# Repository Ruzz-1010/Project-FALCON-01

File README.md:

# Project FALCON-01

<!-- FALCON-DOST-REVISION-NOTE:START -->
> **Current revision note (2026-10-10):** Use the DOST major revision baseline in [`docs/REVISION_2026-10-10.md`](docs/REVISION_2026-10-10.md) unless this file is explicitly archived. The active proposal core is a compact ESP32-based buoy with **water pressure sensing, wind speed/direction sensing, GPS for exact position and security, battery + solar power, and Wi-Fi/LTE internet communication**. LoRa, large Bay Station hardware, tall tower layouts, and continuous every-second uploads are legacy or optional fallback assumptions.
<!-- FALCON-DOST-REVISION-NOTE:END -->

## Active design revision 2026-10-10

The current direction is a smaller compact can-buoy with ESP32 local sampling, water pressure sensing, wind speed/direction sensing, GPS position/security, battery + solar power, event-driven summaries and alerts, direct cloud connectivity through Wi-Fi for laboratory work or 4G/LTE for a remote trial, and a reduced battery selected from measured load. LoRa-primary and large Bay Station assumptions are historical unless explicitly marked otherwise.

cd "/home/ruzz/Documents/PlatformIO/Projects/Project FALCON-01/edge"
python3 -m falcon_edge.service

**Fullbright College's AI-powered Live Coastal Observation Network**

Project FALCON is a Phase 1 coastal monitoring buoy proposal focused on five core subsystems:

1. pressure-derived wave/water behavior monitoring;
2. wind speed and wind direction monitoring;
3. GPS-based exact position and security/drift monitoring;
4. battery and solar power monitoring; and
5. Wi-Fi/LTE internet communication for cloud/dashboard reporting.

Short-term wave-height prediction research remains a software-side analysis option and is not run as heavy processing on the buoy.

The AI scope is limited to short-term wave-height prediction and sea-condition classification as **Calm**, **Moderate**, or **Rough**.

## Source of Truth

[PROJECT_CONTEXT.md v9.0](docs/PROJECT_CONTEXT.md) is the official engineering source of truth.

Working source code remains authoritative for what is currently implemented. Documentation describes both the verified prototype and the approved Phase 1 target; it does not turn planned hardware into implemented hardware.

## Current Status

Status: **Phase 1 Prototype**

Implemented in the repository:

- PlatformIO ESP32 Arduino firmware;
- `FALCON-01` Wi-Fi access point and captive portal;
- LittleFS fallback dashboard and basic ESP32 controls;
- laptop-hosted Python edge/cloud service prototype;
- simulated telemetry and deterministic alert scenarios;
- local SQLite telemetry history;
- presentation forecast and backtest pipeline;
- responsive local dashboard with light/dark mode;
- current-versus-predicted forecast presentation;
- browser notifications and alert history;
- and interactive Fusion-derived 3D buoy visualization.

Current mechanical direction: a compact reference-style can buoy with a round float body, tapered top electronics housing, side solar panels, lower ballast, protected pressure stilling tube, LTE/Wi-Fi antenna, red beacon, and single-anchor mooring. Older spar, large tower, and four-outrigger concepts are retained only as historical studies.

### Safe frontend migration

The production dashboard in `data/` remains the verified fallback. The page-by-page React + TypeScript migration in `dashboard-next/` now includes the responsive shell plus Overview, Wave AI, Motion, GPS, Power, System Health, Alerts, Logs, and Settings. Wave AI includes current-versus-predicted results, forecast horizons, model evidence, and presentation scenarios. Motion preserves the Fusion GLB digital twin with telemetry-driven sea motion, camera controls, navigation lights, and component alert highlighting. GPS provides a live Puerto Princesa coastal map, deployment reference, geofence, and drift telemetry. Power presents battery, solar, thermal, fan, and recent-history telemetry. System Health presents local service connectivity, sensor availability, edge resource use, and diagnostics. Alerts provides live notification badges and toasts, active warnings, persisted history, severity filters, and non-destructive acknowledgement. Logs provides searchable telemetry, AI prediction, alert, and system-event archives with filtered CSV/JSON export. Settings provides local presentation preferences, notification permission, scenarios, and auditable maintenance controls.

Run the migration preview with the edge service on port `8765`:

```powershell
cd dashboard-next
npm install
npm run dev
```

Then open `http://127.0.0.1:5173`.

Important limitations:

- physical Phase 1 sensors are not yet fully integrated;
- the laptop currently represents a development cloud/edge host during demonstrations;
- simulator results are not field-validation results;
- the current presentation forecast is not the final trained AI model;
- and the 3D dashboard assets exceed the configured ESP32 LittleFS capacity.

## Approved Phase 1 Architecture

```text
Marine Sensors -> ESP32 -> Wi-Fi/LTE -> Cloud API/database/dashboard
                         |
                         +-> event detection + buffering
                         +-> slow heartbeat summaries
                         +-> immediate alerts on pressure/motion/GPS/power thresholds
                         +-> dashboard -> laptop / tablet / phone
```

Direct cloud connectivity is the revised Phase 1 direction. Wi-Fi is used for laboratory testing; 4G/LTE is the remote field path after modem, SIM/data, antenna, endpoint security, buffering, and coverage tests are approved.

## Approved Primary Sensor Set

- water-pressure sensor for pressure-derived wave estimation;
- wind-speed sensor; and
- wind-direction sensor.

GPS, battery/solar status, timestamps, and security states are supporting system telemetry only. Water temperature, BNO085, salinity, conductivity, and other environmental sensors are excluded from Phase 1.

pH, salinity, turbidity, dissolved oxygen, rain, UV, cameras, hydrophones, current meters, and Water Quality Index inputs are Future Expansion.

## Approved AI Outputs

- current wave height;
- predicted wave height for a 5–15 minute horizon;
- prediction confidence or quality indicator;
- prediction status and model version;
- and sea condition: Calm, Moderate, or Rough.

Weather, typhoon, storm, ocean-current, fish, maintenance, camera, and water-quality predictions are not part of Phase 1.

## Approved API Direction

```text
GET  /status
GET  /wave
GET  /gps
GET  /battery
GET  /solar
GET  /ai
POST /restart
POST /calibrate
```

Current `/api/...` endpoints are prototype compatibility routes and require a controlled migration to the approved v4 contract.

## Development Setup

### ESP32 Firmware

```powershell
platformio run
platformio run --target buildfs
platformio run --target upload
platformio run --target uploadfs
```

Close the serial monitor before uploading. Hold BOOT if required; after flashing, release BOOT and press EN/RESET.

Prototype access-point settings:

| Setting | Value |
| --- | --- |
| SSID | `FALCON-01` |
| Prototype password | `falcon123` |
| ESP32 dashboard | `http://192.168.4.1` |

The prototype password must be changed before field deployment.

### Laptop Edge-Service Demonstration

```powershell//windos
cd "C:\Users\Admin\Documents\PlatformIO\Projects\Project FALCON-01\edge"
python -m falcon_edge.service
```
terminal//linux
cd "/home/ruzz/Documents/PlatformIO/Projects/Project FALCON-01/edge"
python3 -m falcon_edge.service

Open `http://127.0.0.1:8765/`.

Run tests:

```powershell
cd edge
python -m unittest discover -s tests -v
```

## Repository Today

```text
Project FALCON-01/
├── data/               # current dashboard assets and 3D model
├── docs/               # engineering documentation
├── edge/               # laptop-hosted edge/cloud service prototype
├── exports/            # archived CAD exchange assets
├── fusion360/          # mechanical component documentation
├── include/            # ESP32 configuration headers
├── src/                # ESP32 firmware source
├── test/               # PlatformIO test location
├── platformio.ini
└── README.md
```

The target v4 repository organization is documented in PROJECT_CONTEXT.md and will be adopted incrementally without breaking working code.

## Documentation

Start here:

1. [PROJECT_CONTEXT.md](docs/PROJECT_CONTEXT.md) — master engineering context;
2. [ROADMAP.md](docs/ROADMAP.md) — focused delivery gates;
3. [HARDWARE.md](docs/HARDWARE.md) — electronics and sensor baseline;
4. [SOFTWARE.md](docs/SOFTWARE.md) — firmware and edge-software boundaries;
5. [AI.md](docs/AI.md) — focused prediction and classification specification;
6. [DASHBOARD.md](docs/DASHBOARD.md) — approved information architecture;
7. [API.md](docs/API.md) — approved REST contract and migration status;
8. [INDEX.md](docs/INDEX.md) — full documentation index.

## Engineering Principles

- Focus over feature count.
- Reliability over decoration.
- Local-first operation.
- Measured, estimated, predicted, simulated, and unavailable values must remain distinguishable.
- No field claim without calibration and evidence.
- No AI claim outside wave prediction and three-class sea-condition classification.
- Preserve working source and migrate incrementally.

## Future Expansion

Satellite communication, multi-buoy networking, mobile applications, water-quality sensing, computer vision, additional AI models, autonomous capabilities, and LoRa fallback are outside the reduced Phase 1 minimum build. The revised path uses event-driven Wi-Fi/LTE upload directly from the ESP32 buoy to the selected cloud/development service, subject to hardware, security, coverage, power, and site validation.

## Revision History

| Version | Date | Change |
| --- | --- | --- |
| 3.1 | 2026-08-05 | Added source-verified implementation status. |
| 4.0 | 2026-08-09 | Aligned repository entry point with PROJECT_CONTEXT.md v4.0 and the focused wave-monitoring research scope. |
| 5.0 | 2026-08-13 | Adopted the single-body rounded-keel buoy baseline and retired the four-stabilizer arrangement to legacy status. |

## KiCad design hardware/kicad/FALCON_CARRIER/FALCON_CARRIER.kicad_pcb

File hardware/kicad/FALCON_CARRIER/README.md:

# FALCON-01 Low-Voltage Carrier PCB

<!-- FALCON-DOST-REVISION-NOTE:START -->
> **Current revision note (2026-10-10):** Use the DOST major revision baseline in [`docs/REVISION_2026-10-10.md`](../../../docs/REVISION_2026-10-10.md) unless this file is explicitly archived. The active proposal core is a compact ESP32-based buoy with **water pressure sensing, wind speed/direction sensing, GPS for exact position and security, battery + solar power, and Wi-Fi/LTE internet communication**. LoRa, large Bay Station hardware, tall tower layouts, and continuous every-second uploads are legacy or optional fallback assumptions.
<!-- FALCON-DOST-REVISION-NOTE:END -->

> **HISTORICAL ELECTRICAL DRAFT:** This project predates the Bay Station/LTE baseline and still contains a BNO085 footprint plus Orange Pi/USB assumptions. Do not fabricate it. Rebuild the release schematic/PCB only after exact sensors, LTE modem/power/interface, connectors, and mechanical interfaces are approved.

Status: **native KiCad pre-schematic and placement-zone draft; not approved for
fabrication**.

This KiCad project will implement a serviceable low-voltage carrier for the
ESP32 DevKit and selected sensor breakouts. It intentionally excludes the raw
12.8 V battery, solar-panel, MPPT, and high-current distribution paths.

## Board boundary

The board receives protected, regulated 5 V from the dedicated ESP32 buck
branch. It distributes 5 V, regulated 3.3 V, logic ground, and the validated
sensor buses. The Orange Pi retains its own 5 V supply and connects to the
ESP32 through USB during Phase 1.

High-current battery and solar conductors connect directly to the appropriately
rated INA260 breakout terminals outside the carrier copper path. Only INA260
logic power and I2C reach the carrier.

## Draft modules

- Socketed ESP32 DevKit / ESP-WROOM-32 class controller.
- Socketed Adafruit BNO085 SPI breakout.
- historical Bar02 I2C connector, which must be replaced by the HPT604 4–20 mA receiver before fabrication.
- GPS UART connector.
- Separate battery and solar INA260 logic connectors.
- MCP9808 and ADS1115 module connectors.
- Wind-speed, wind-vane, optional DS18B20, and leak-sensor connectors.
- Fan MOSFET driver placeholder; component values remain TBD.
- Protected 5 V input and 3.3 V sensor-regulator placeholder.

## Mechanical starting envelope

The current control deck is documented as 250 x 210 mm inside the latest
rectangular-pod concept. The first carrier outline shall be no larger than
165 x 125 mm, leaving service and connector clearance. This is a planning
envelope only: mounting-hole coordinates and final outline remain TBD until the
enclosure and modules are physically measured.

## Native KiCad files

Native KiCad 10 `.kicad_pro`, `.kicad_sch`, and `.kicad_pcb` files are present.
The board contains a 165 x 125 mm compact-preview outline and labeled placement zones,
not final footprints or routing. Do not manufacture from placeholder geometry
or exported pictures.

Schematic v1.0 is organized into Power Management, ESP32 Controller, Sensor
Interfaces, Communication, and Debug & Expansion blocks. It adds the documented
battery protection chain, external-MPPT solar boundary, power-only service
USB-C, status/program controls, eight release test points, and connector-only
UART edge interface. The external edge computer is not part of the PCB.
`generate_schematic.py` reproducibly rebuilds the native schematic and project
symbol library. The current placement PCB predates v1.0 and must not be routed
until schematic-to-PCB synchronization and the remaining part-selection gates
are completed.

PCB placement v0.7 contains manufacturer-CAD module sockets, official-catalog
JST GH/VH connector geometry, named-net pads, four provisional M3 mounting holes, and an ESP32 antenna
keep-out. `generate_pcb.py` reproducibly builds this placement. The current DRC
result is **zero geometry/rule violations and 64 expected unconnected ratsnest
items**. Those connections must remain visible until deliberate copper routing;
they are not to be suppressed or described as a finished PCB.

Industrial placement v2.0 preserves the existing PCB pad/net assignments and
the 165 x 125 mm outline while reorganizing all 55 footprints. GPS, BNO085,
pressure, wind-speed, wind-direction, temperature, battery-monitor, and
solar-monitor interfaces follow one outward-facing sensor edge; the ESP32 is
centered; power follows one lower-edge service flow; communication/test points
form an accessible bank; and fan circuitry occupies a separate corner.
`professional_placement.py` reapplies this placement deterministically. This is
a routing-ready placement candidate, not a fabrication release: the physical
footprint, enclosure, and part-selection gates still apply.

Placement v0.3 reorganizes the same validated nets into professional functional
zones: field connectors on the left service edge, I2C modules in an addressable
distribution column, pull-ups beside their inputs, BNO085/GPS in the quiet
control area, ESP32 at the antenna edge, and power/fan/service components at the
bottom right. This reduces ratsnest crossing before routing without pretending
that the provisional footprints are final.

Placement v0.4 adds 18 schematic-synchronized, through-hole service test points
for both rails, ground, I2C, BNO085 SPI/control, GPS UART, external sensor
inputs, and fan PWM. They are grouped and labeled in an accessible service bank
for safe bench bring-up; this does not remove the footprint-validation gate.

Placement v0.5 replaces the generic U3, J3, J4, J5, and U4 envelopes with
manufacturer-CAD socket geometry for the selected Adafruit BNO085, Ultimate
GPS, two INA260 boards, and ADS1115 STEMMA QT board. Header pads, module
outlines, and mounting holes now use the official board datums. U2 was also
rotated so its antenna end actually faces the right-edge keep-out. Receiving
and 1:1 checks are still mandatory before routing or fabrication.

Placement v0.6 adds the reviewed external-input protection blocks: J1 raw 5 V,
U6 TPS25947-family eFuse candidate, and JP1 external-power enable. The normal
deployment remains USB powered with JP1 open. The added silkscreen explicitly
requires USB removal before JP1 is fitted. Protection values remain blocked by
load, buck, transient, and thermal measurements.

Reference map:

| Reference | Function |
| --- | --- |
| U1 | 5 V to 3.3 V regulator placeholder |
| U2 | ESP32 DevKit carrier interface |
| U3 | BNO085 SPI breakout |
| U4 | ADS1115 wind-vane ADC |
| U5 | Fan MOSFET-driver placeholder |
| U6 | TPS25947-family external-input eFuse candidate |
| JP1 | External-power enable shunt; USB must be unplugged when fitted |
| J1 | Protected 5 V input |
| J2–J6 | Historical Bar02, GPS, two INA260 logic links, MCP9808; J2 requires HPT604 loop redesign |
| J7–J10 | Anemometer, wind vane, DS18B20, leak sensor |
| J11/J13 | Independent four-wire PWM fan outputs |
| J12 | Service I2C |
| R1–R2 | Wind-pulse 10 kOhm and OneWire 4.7 kOhm pull-ups |
| H1–H4 | Provisional M3 mounting holes |
| TP1–TP18 | Labeled power, bus, UART, sensor-input, and PWM test points |

Every footprint still requires a purchased-part check on a 1:1 print. The JST
GH/VH geometry is captured from the official manufacturer catalogs, but mating
direction, assembly clearance, and received-part revision must still be signed
off before fabrication.

The next release gate is [FOOTPRINT_VALIDATION.md](FOOTPRINT_VALIDATION.md).
Record measurements in `footprint_measurements.csv`; do not start final copper
routing while the critical rows remain `PENDING`.
Use [PHYSICAL_FIT_CHECKLIST.md](PHYSICAL_FIT_CHECKLIST.md) with a true 100%-scale
print to capture the required module, connector, cable, and enclosure checks.
Run `python3 export_physical_fit_sheet.py`, then print
`FALCON_CARRIER_PHYSICAL_FIT_A4.svg` on A4 portrait at **100% / Actual size**.
Verify its 50 mm calibration bar before trusting the footprint overlay.
On Linux Mint, a matching A4 PDF can be rebuilt with
`convert -density 300 FALCON_CARRIER_PHYSICAL_FIT_A4.svg -units PixelsPerInch FALCON_CARRIER_PHYSICAL_FIT_A4.pdf`.

Official product dimensions and CAD-derived hole/header coordinates gathered
for that gate are recorded in
[MANUFACTURER_DIMENSION_RESEARCH.md](MANUFACTURER_DIMENSION_RESEARCH.md).
These references reduce guesswork but do not replace the receiving and 1:1 checks.

KiCad routing classes and the required routing sequence are documented in
[ROUTING_PLAN.md](ROUTING_PLAN.md). The project now applies wider power/fan
rules and separate sensor-bus/external-sensor clearances automatically.

U2 is now locked to the official **Espressif ESP32-DevKitC V4 with
ESP32-WROOM-32E** 38-pad geometry and header numbering. The official Espressif
KiCad footprint and its license are stored under `vendor/`; the generated board
uses the same pad pitch, row spacing, outline, USB end, and approved functional
pad mapping. Physical receiving/1:1 validation is still required.

Use these source registers during capture:

- [NET_REGISTER.csv](NET_REGISTER.csv)
- [CONNECTOR_REGISTER.md](CONNECTOR_REGISTER.md)
- [CONNECTOR_SELECTION_BASELINE.md](CONNECTOR_SELECTION_BASELINE.md)
- [CONNECTOR_HARNESS_PLAN.md](CONNECTOR_HARNESS_PLAN.md)
- [CONNECTOR_ORIENTATION_AUDIT.md](CONNECTOR_ORIENTATION_AUDIT.md)
- [POWER_PROTECTION_BASELINE.md](POWER_PROTECTION_BASELINE.md)
- [FAN_SELECTION_BASELINE.md](FAN_SELECTION_BASELINE.md)
- [SENSOR_POWER_BASELINE.md](SENSOR_POWER_BASELINE.md)
- [DESIGN_RULES.md](DESIGN_RULES.md)
- [`docs/PCB_VALIDATION_REGISTER.md`](../../../docs/PCB_VALIDATION_REGISTER.md)

## Release gates

1. Record exact board revisions, dimensions, and pin labels.
2. Close every Critical item in `docs/PCB_VALIDATION_REGISTER.md`.
3. Verify source selection prevents USB/external-5V backfeed.
4. Pass ERC with every exception documented.
5. Print footprints at 1:1 and place the actual modules on the print.
6. Pass DRC and an independent connector/polarity review.
7. Assemble and test one protected bench prototype before any marine trial.

## 3D preview

Local lightweight VRML envelopes are stored in `models/` and attached by the
PCB generator. Run `python3 generate_3d_models.py`, regenerate the PCB, open
`FALCON_CARRIER.kicad_pcb` in KiCad PCB Editor, then press **Alt+3**. These
models communicate placement and approximate component volume only; they are
not manufacturer STEP models and must not be used for enclosure tolerancing.

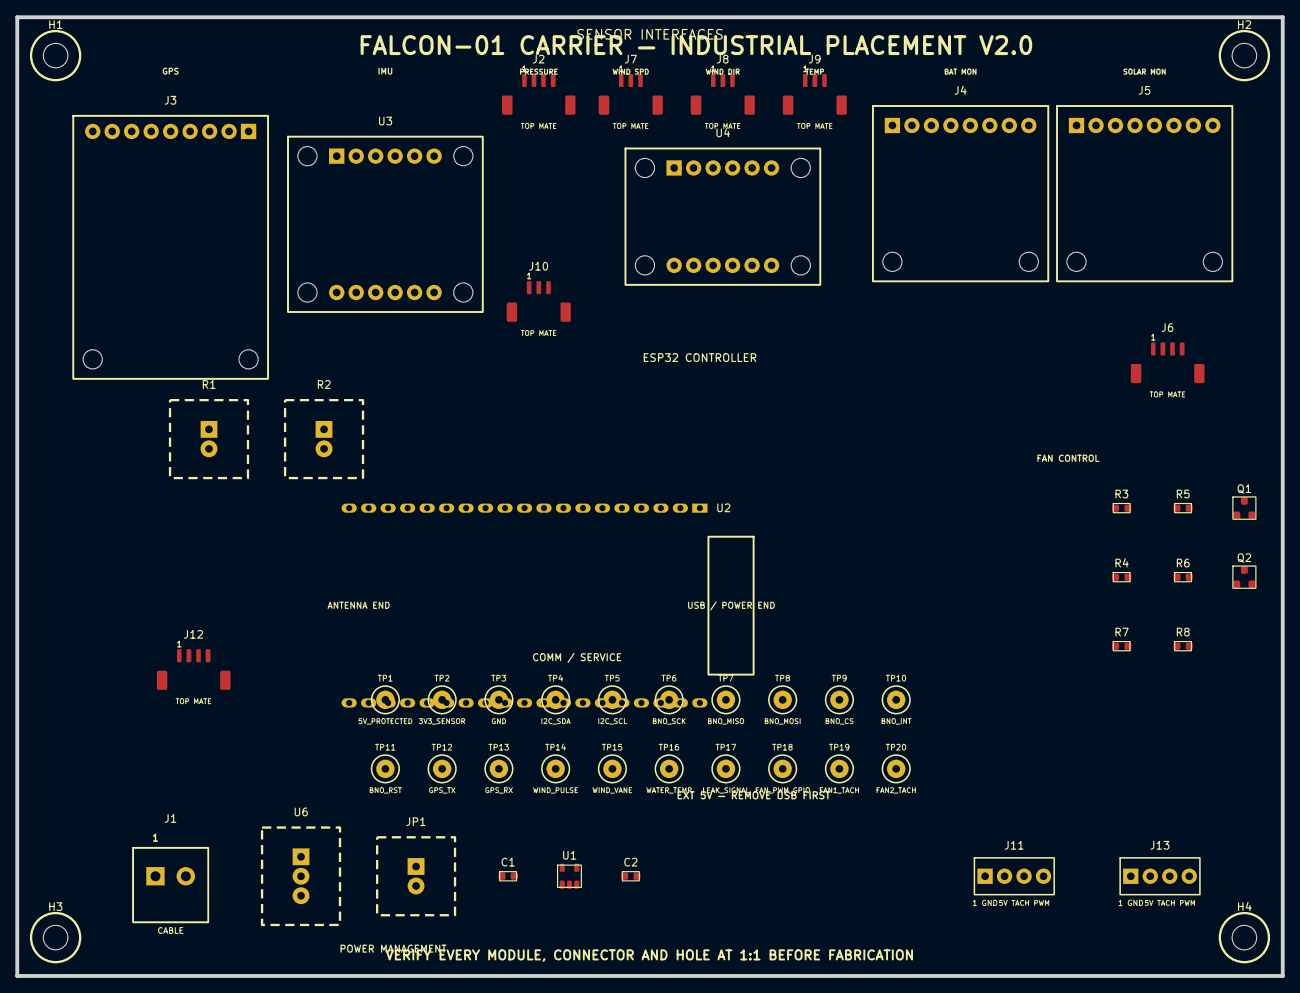
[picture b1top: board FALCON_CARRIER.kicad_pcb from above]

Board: 2 copper layers, 165.0 x 125.0 mm, 55 parts (0 on the bottom side), 26 nets, no tracks yet.

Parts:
C1: LDO_INPUT_1UF_X7R; R_0603_1608Metric
C2: LDO_OUTPUT_1UF_X7R; R_0603_1608Metric
H1, H2, H3, H4: M3 PROVISIONAL; FALCON_PROVISIONAL_M3_HOLE
J1: B2P-VH-FB-B; JST_VH_02P_B2P-VH-FB-B
J2, J6, J12: BM04B-GHS-TBT; JST_GH_04P_TOP_BM04B-GHS-TBT
J3: GPS_UART; FALCON_LOCKED_GPS_UART
J4: INA260_BAT_LOGIC; FALCON_LOCKED_INA260_BAT_LOGIC
J5: INA260_SOLAR_0X41; FALCON_LOCKED_INA260_SOLAR_0X41
J7, J8, J9, J10: BM03B-GHS-TBT; JST_GH_03P_TOP_BM03B-GHS-TBT
J11, J13: 470531000; MOLEX_470531000_4PIN_FAN_HEADER
JP1: EXT_POWER_ENABLE; FALCON_PROVISIONAL_EXT_POWER_ENABLE
Q1: 2N7002_FAN1_PWM; SOT-23_2N7002
Q2: 2N7002_FAN2_PWM; SOT-23_2N7002
R1: PULLUP_10K; FALCON_PROVISIONAL_PULLUP_10K
R2: PULLUP_4K7; FALCON_PROVISIONAL_PULLUP_4K7
R3: FAN1_GATE_100R; R_0603_1608Metric
R4: FAN2_GATE_100R; R_0603_1608Metric
R5: FAN1_GATE_PULLDOWN_100K; R_0603_1608Metric
R6: FAN2_GATE_PULLDOWN_100K; R_0603_1608Metric
R7: FAN1_TACH_PULLUP_10K; R_0603_1608Metric
R8: FAN2_TACH_PULLUP_10K; R_0603_1608Metric
TP1: 5V_PROTECTED; FALCON_TEST_POINT_THT
TP2: 3V3_SENSOR; FALCON_TEST_POINT_THT
TP3: GND; FALCON_TEST_POINT_THT
TP4: I2C_SDA; FALCON_TEST_POINT_THT
TP5: I2C_SCL; FALCON_TEST_POINT_THT
TP6: BNO_SCK; FALCON_TEST_POINT_THT
TP7: BNO_MISO; FALCON_TEST_POINT_THT
TP8: BNO_MOSI; FALCON_TEST_POINT_THT
TP9: BNO_CS; FALCON_TEST_POINT_THT
TP10: BNO_INT; FALCON_TEST_POINT_THT
TP11: BNO_RST; FALCON_TEST_POINT_THT
TP12: GPS_TX; FALCON_TEST_POINT_THT
TP13: GPS_RX; FALCON_TEST_POINT_THT
TP14: WIND_PULSE; FALCON_TEST_POINT_THT
TP15: WIND_VANE; FALCON_TEST_POINT_THT
TP16: WATER_TEMP; FALCON_TEST_POINT_THT
TP17: LEAK_SIGNAL; FALCON_TEST_POINT_THT
TP18: FAN_PWM_GPIO; FALCON_TEST_POINT_THT
TP19: FAN1_TACH; FALCON_TEST_POINT_THT
TP20: FAN2_TACH; FALCON_TEST_POINT_THT
U1: AP2112K-3.3TRG1; SOT-25_AP2112K
U2: ESP32-DevKitC_V4_WROOM-32E; FALCON_LOCKED_ESP32_DEVKITC_V4
U3: BNO085_SPI; FALCON_LOCKED_BNO085_SPI
U4: ADS1115_0X48; FALCON_LOCKED_ADS1115_0X48
U6: EFUSE_TPS25947_TBD; FALCON_PROVISIONAL_EFUSE_TPS25947_TBD

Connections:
+3V3_SENSOR: C2.1, J2.1, J3.2, J4.1, J5.1, J6.1, J7.1, J8.1, J9.1, J10.1, J12.1, R1.1, R2.1, R7.1, R8.1, TP2.1, U1.5, U3.A1, U3.B2, U3.B3, U4.B1
+5V_EXT_PROTECTED: JP1.1, U6.3
+5V_INPUT_RAW: J1.1, U6.1
+5V_PROTECTED: C1.1, J11.2, J13.2, JP1.2, TP1.1, U1.1, U1.3, U2.19
BNO_CS: TP9.1, U2.15, U3.B6
BNO_INT: TP10.1, U2.11, U3.A6
BNO_MISO: TP7.1, U2.31, U3.A5
BNO_MOSI: TP8.1, U2.37, U3.B5
BNO_RST: TP11.1, U2.12, U3.B4
BNO_SCK: TP6.1, U2.30, U3.A4
FAN1_GATE: Q1.1, R3.2, R5.1
FAN1_PWM_OD: J11.4, Q1.3
FAN1_TACH: J11.3, R7.2, TP19.1, U2.5
FAN2_GATE: Q2.1, R4.2, R6.1
FAN2_PWM_OD: J13.4, Q2.3
FAN2_TACH: J13.3, R8.2, TP20.1, U2.6
FAN_PWM_GPIO: R3.1, R4.1, TP18.1, U2.8
GND: C1.2, C2.2, J1.2, J2.4, J3.3, J4.2, J5.2, J6.4, J7.3, J8.3, J9.3, J10.3, J11.1, J12.4, J13.1, Q1.2, Q2.2, R5.2, R6.2, TP3.1, U1.2, U2.14, U2.32, U2.38, U3.A3, U4.B2, U6.2
GPS_RX: J3.4, TP13.1, U2.28
GPS_TX: J3.5, TP12.1, U2.27
I2C_SCL: J2.2, J4.3, J5.3, J6.2, J12.2, TP5.1, U2.36, U4.B3
I2C_SDA: J2.3, J4.4, J5.4, J6.3, J12.3, TP4.1, U2.33, U4.B4
LEAK_SIGNAL: J10.2, TP17.1, U2.7
WATER_TEMP: J9.2, R2.2, TP16.1, U2.10
WIND_PULSE: J7.2, R1.2, TP14.1, U2.9
WIND_VANE: J8.2, TP15.1, U4.A5

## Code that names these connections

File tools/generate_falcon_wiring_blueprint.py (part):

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    # GPS board with ceramic patch antenna and u.FL.
    art='''<path d="M18 45H160V132H18Z" class="detail"/><rect x="35" y="58" width="62" height="55" class="detail"/><path d="M112 58h32v26h-32m0 14h32m-32 12h32" class="fine"/><circle cx="148" cy="120" r="5" class="detail"/><path d="M30 132v14m20-14v14m20-14v14m20-14v14" class="fine"/>'''
    s.append(device(58,335,185,165,"ADAFRUIT ULTIMATE GPS","S02",art))
    s += [text(258,377,"J3 · MODULE HEADER","net"),text(258,400,"PAD 2  +3V3_SENSOR","txt"),text(258,420,"PAD 3  GND","txt"),text(258,440,"PAD 4  GPS_RX ← GPIO17","txt"),text(258,460,"PAD 5  GPS_TX → GPIO16","txt"),text(258,485,"TX/RX cross at the controller.","small")]

    # Weather meter with cups and vane.
    art='''<path d="M90 45v92M55 72h70M90 72L58 52M90 72l32-20M58 52a17 10 0 1 0 0-18M122 52a17 10 0 1 1 0-18M90 72v-25" class="detail"/><path d="M112 108h42l-22-18v36zM112 108H72" class="detail"/><path d="M78 137h25v15H78" class="fine"/>'''
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          '<path d="M460 770H545V280" class="i2c"/><path d="M460 785H560V310" class="i2c"/>',
          '<path d="M460 420H585V360H707" class="uart"/>',text(475,412,"GPS_TX → RX2","net"),
          '<path d="M460 440H600V390H707" class="uart"/>',text(475,455,"GPS_RX ← TX2","net"),
          '<path d="M460 600H625V470H707" class="gpio"/>',text(475,592,"WIND_PULSE","net"),
          '<path d="M460 640H650V160H970V250H955" class="gpio"/>',text(475,660,"WIND_VANE → ADS1115 A0","net")]

    # Supporting breakout cards beside MCU.
    ads='''<path d="M18 48H142V125H18Z" class="detail"/><rect x="56" y="66" width="44" height="38" class="detail"/><path d="M25 58h20m-20 15h20m-20 15h20m-20 15h20m70-45h20m-20 15h20m-20 15h20m-20 15h20" class="fine"/>'''
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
